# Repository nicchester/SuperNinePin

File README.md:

# SuperNinePin Controller Adaptor

Converts a Super Nintendo controller to an Amiga/Commodore 64 controller, using digital logic. (none of this microcontroller nonsense)

### Why do such a thing? 

It's easy to throw a microcontroller at everything, and it ocurred to me I haven't done much useful in pure digital logic with the lowest possible IC count. So this is just for the fun of doing it, and also it's quite a fitting project for a 'vintage' use case. 

---

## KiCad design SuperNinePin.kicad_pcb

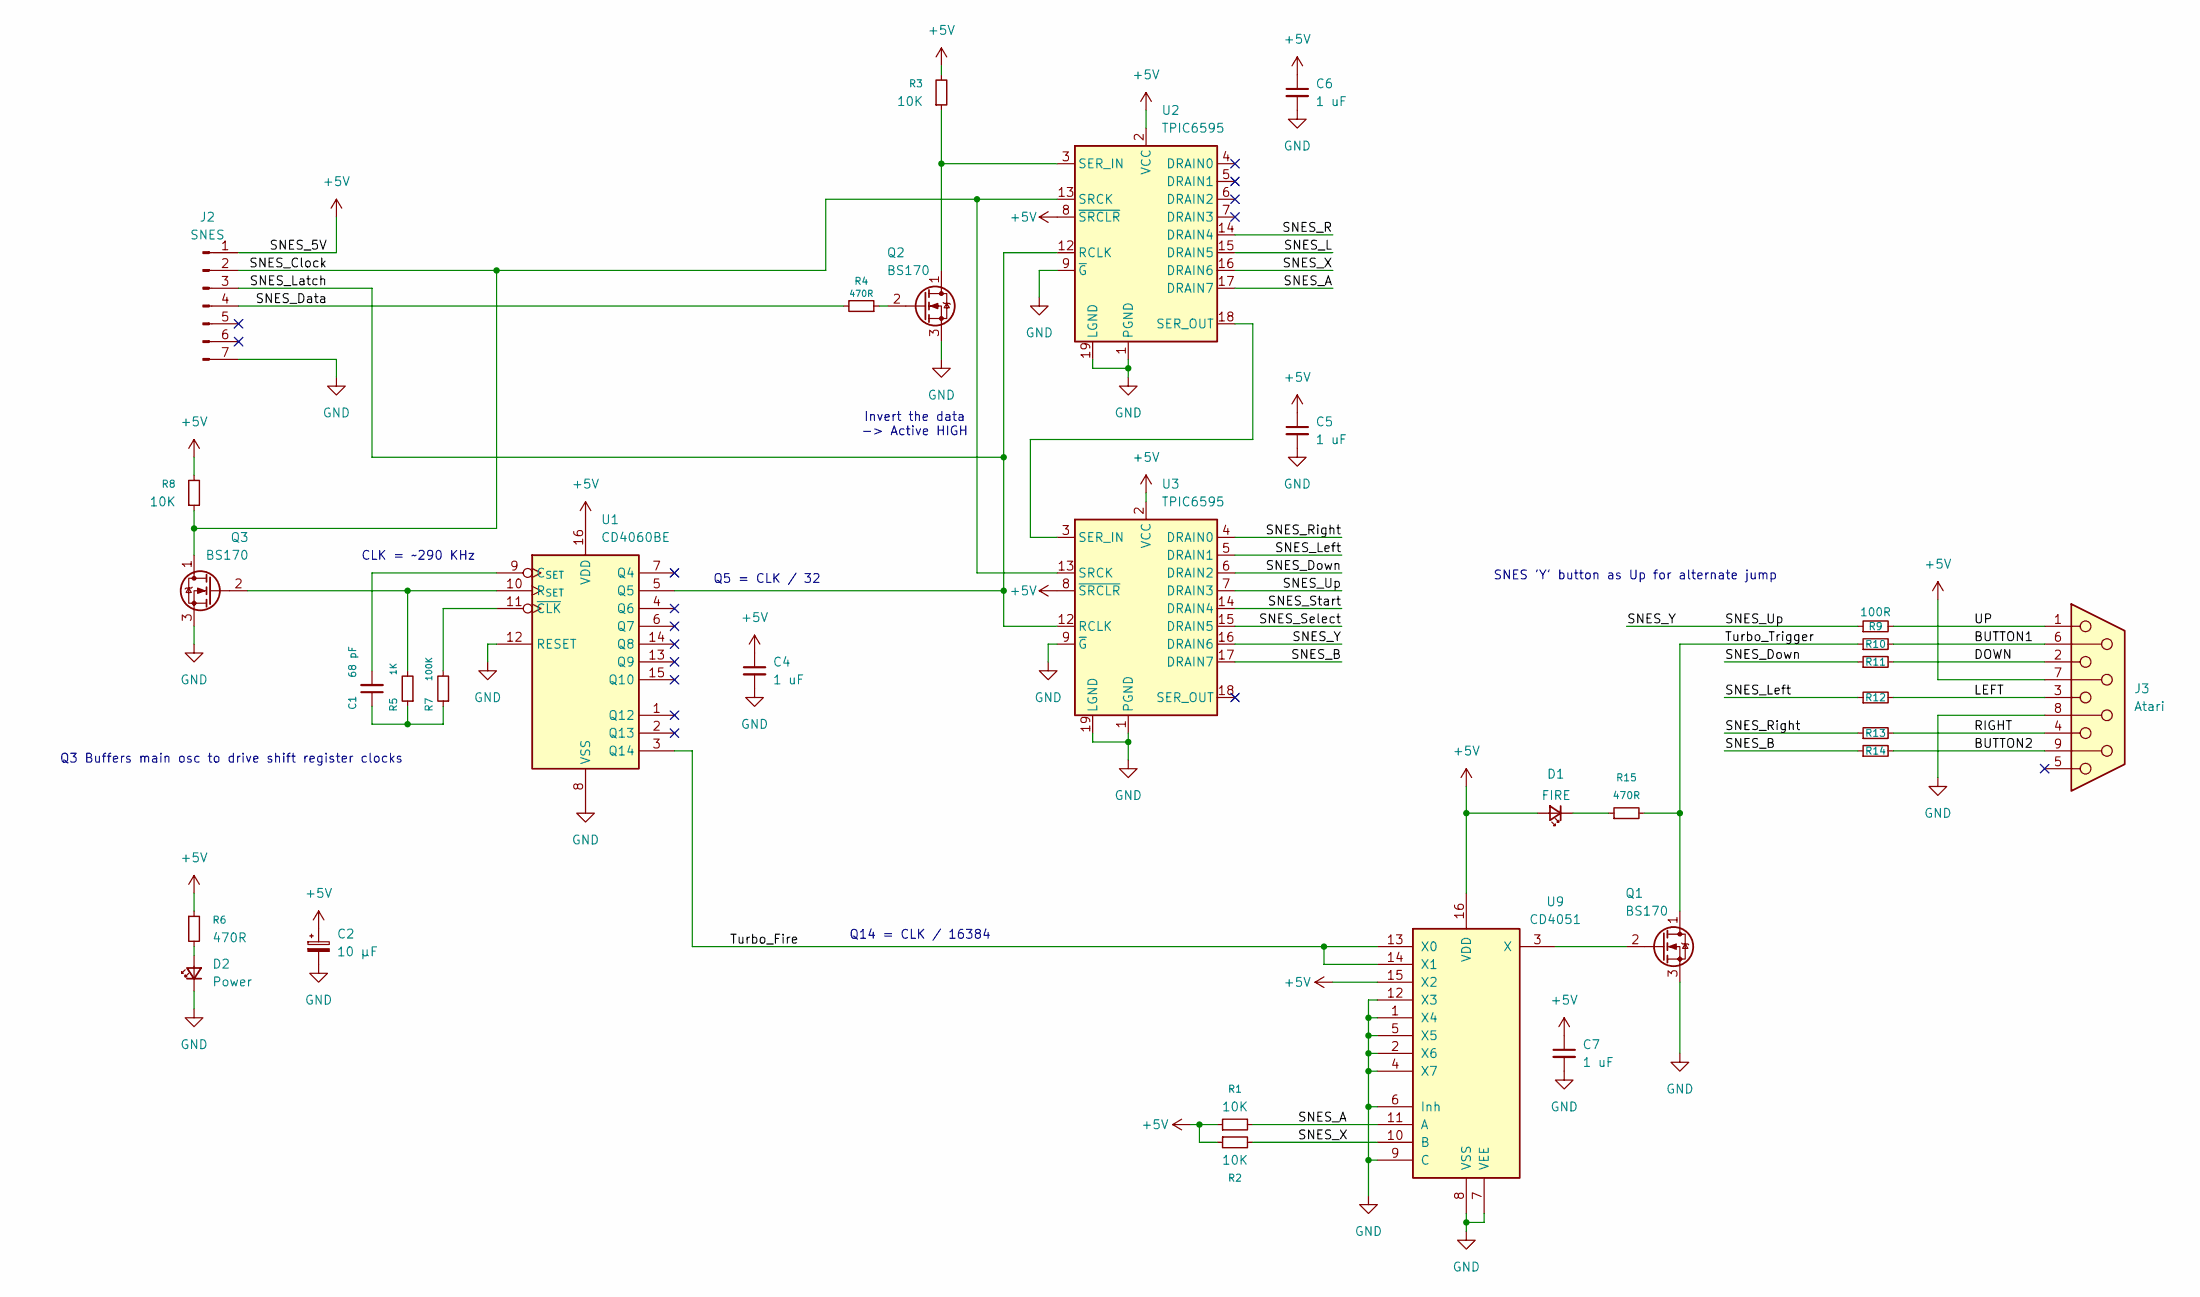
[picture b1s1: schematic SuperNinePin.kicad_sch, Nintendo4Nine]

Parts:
C1: 68 pF; C_Disc_D3.4mm_W2.1mm_P2.50mm
C2: 10 µF; C_Radial_D5.0mm_H5.0mm_P2.00mm
C4, C5, C6, C7: 1 uF; C_Disc_D3.0mm_W1.6mm_P2.50mm
D1: FIRE; LED_D3.0mm
D2: Power; LED_D3.0mm
J2: SNES; SNESController
J3: Atari; DSUB-9_Pins_Horizontal_P2.77x2.84mm_EdgePinOffset4.94mm_Hou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
Q1, Q2, Q3: BS170; TO-92_Inline_Wide
R1, R2, R3, R8: 10K; R_Axial_DIN0207_L6.3mm_D2.5mm_P10.16mm_Horizontal
R4, R6, R15: 470R; R_Axial_DIN0207_L6.3mm_D2.5mm_P10.16mm_Horizontal
R5: 1K; R_Axial_DIN0207_L6.3mm_D2.5mm_P10.16mm_Horizontal
R7: 100K; R_Axial_DIN0207_L6.3mm_D2.5mm_P10.16mm_Horizontal
R9, R10, R11, R12, R13, R14: 100R; R_Axial_DIN0207_L6.3mm_D2.5mm_P10.16mm_Horizontal
U1: CD4060BE; DIP-16_W7.62mm
U2, U3: TPIC6595; DIP-20_W7.62mm
U9: CD4051; DIP-16_W7.62mm

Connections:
+5V: C2.1, C4.1, C5.1, C6.1, C7.1, D1.2 (A), J2.1, J3.7, R1.1, R2.1, R3.2, R6.1, R8.2, U1.16 (VDD), U2.2 (VCC), U2.8 (~SRCLR), U3.2 (VCC), U3.8 (~SRCLR), U9.15 (X2), U9.16 (VDD)
/BUTTON1: J3.6, R10.2
/BUTTON2: J3.9, R14.2
/DOWN: J3.2, R11.2
/LEFT: J3.3, R12.2
/RIGHT: J3.4, R13.2
/SNES_A: R1.2, U2.17 (DRAIN7), U9.11 (A)
/SNES_B: R14.1, U3.17 (DRAIN7)
/SNES_Clock: J2.2, Q3.1 (D), R8.1, U2.13 (SRCK), U3.13 (SRCK)
/SNES_Data: J2.4, R4.2
/SNES_Down: R11.1, U3.6 (DRAIN2)
/SNES_L: U2.15 (DRAIN5)
/SNES_Latch: J2.3, U1.5 (Q5), U2.12 (RCLK), U3.12 (RCLK)
/SNES_Left: R12.1, U3.5 (DRAIN1)
/SNES_R: U2.14 (DRAIN4)
/SNES_Right: R13.1, U3.4 (DRAIN0)
/SNES_Select: U3.15 (DRAIN5)
/SNES_Start: U3.14 (DRAIN4)
/SNES_Up: R9.1, U3.7 (DRAIN3), U3.16 (DRAIN6)
/SNES_X: R2.2, U2.16 (DRAIN6), U9.10 (B)
/Turbo_Fire: U1.3 (Q14), U9.13 (X0), U9.14 (X1)
/Turbo_Trigger: Q1.1 (D), R10.1, R15.2
/UP: J3.1, R9.2
GND: C2.2, C4.2, C5.2, C6.2, C7.2, D2.1 (K), J2.7, J3.8, Q1.3 (S), Q2.3 (S), Q3.3 (S), U1.8 (VSS), U1.12 (RESET), U2.1 (PGND), U2.9 (~G), U2.10 (PGND), U2.11 (PGND), U2.19 (LGND), U2.20 (PGND), U3.1 (PGND), U3.9 (~G), U3.10 (PGND), U3.11 (PGND), U3.19 (LGND), U3.20 (PGND), U9.1 (X4), U9.2 (X6), U9.4 (X7), U9.5 (X5), U9.6 (Inh), U9.7 (VEE), U9.8 (VSS), U9.9 (C), U9.12 (X3)
unnamed: C1.1, R5.1, R7.1
unnamed: D1.1 (K), R15.1
unnamed: D2.2 (A), R6.2
unnamed: Q1.2 (G), U9.3 (X)
unnamed: Q2.1 (D), R3.1, U2.3 (SER_IN)
unnamed: Q2.2 (G), R4.1
unnamed: Q3.2 (G), R5.2, U1.10 (R_{SET})
unnamed: C1.2, U1.9 (C_{SET})
unnamed: R7.2, U1.11 (~CLK)
unnamed: U2.18 (SER_OUT), U3.3 (SER_IN)

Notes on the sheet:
Q14 = CLK / 16384
SNES 'Y' button as Up for alternate jump
Invert the data -> Active HIGH
Q5 = CLK / 32
Q3 Buffers main osc to drive shift register clocks
CLK = ~290 KHz

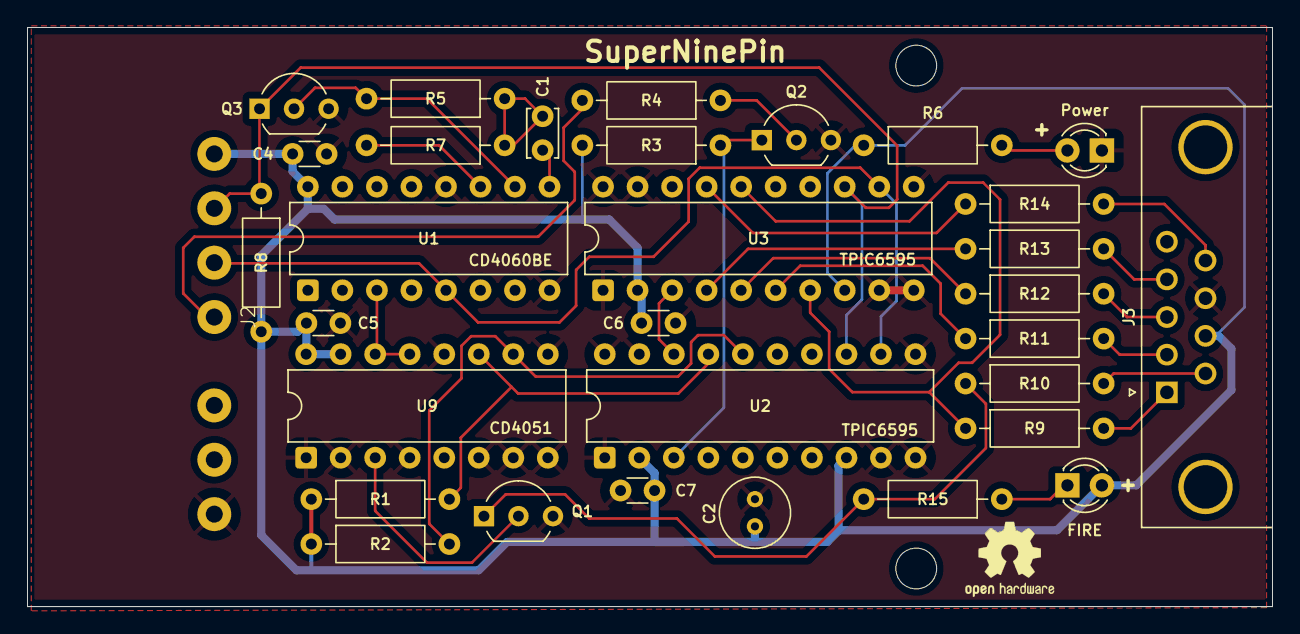
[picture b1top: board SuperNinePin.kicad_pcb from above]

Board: 2 copper layers, 91.6 x 42.6 mm, 32 parts (0 on the bottom side), 30 nets.

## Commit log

2025-12-03 Adds kicad & simulation project files
2025-12-03 Swaps 555 + 4040 for 4060, swaps 74HC595 for TPIC6595
2025-12-31 Adds gerbers, crude enclosure
2026-01-01 Adds image to readme
